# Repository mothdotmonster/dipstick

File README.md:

# WARNING!
when i ordered a batch of these they didn't work and i have no idea why, i think the chips might just have been busted.

do not follow this design as a reference at all. i am only leaving it up for archival purposes.
# dipstick
DIP-sized attinyxx6 breakout board with USB-C

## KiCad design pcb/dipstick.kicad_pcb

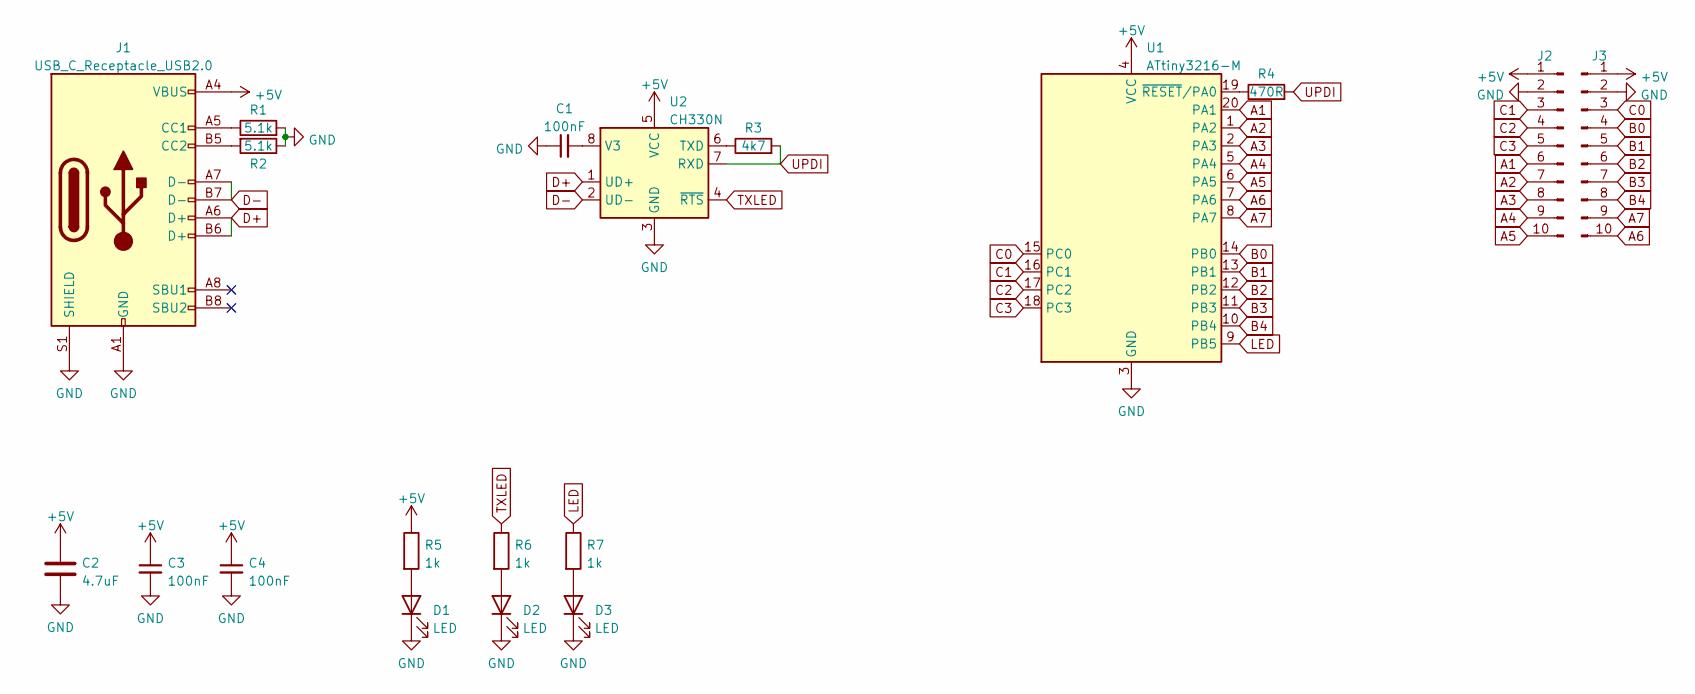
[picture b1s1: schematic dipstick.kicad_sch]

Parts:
C1, C3, C4: 100nF; C_0402_1005Metric; JLC C1525
C2: 4.7uF; C_0402_1005Metric; JLC C23733
D1, D2, D3: LED; LED_0603_1608Metric; JLC C2286
J1: USB_C_Receptacle_USB2.0; USB_C_Receptacle_HRO_TYPE-C-31-M-12; JLC C165948
J2, J3: Conn_01x10_Male; PinHeader_1x10_P2.54mm_Vertical
R1, R2: 5.1k; R_0402_1005Metric; JLC C25905
R3: 4k7; R_0402_1005Metric; JLC C25900
R4: 470R; R_0402_1005Metric; JLC C25117
R5, R6, R7: 1k; R_0402_1005Metric; JLC C11702
U1: ATtiny3216-M; VQFN-20-1EP_3x3mm_P0.4mm_EP1.7x1.7mm; JLC C507118
U2: CH330N; SOIC-8_3.9x4.9mm_P1.27mm; JLC C2977777

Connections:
+5V: C2.1, C3.1, C4.1, J1.A4 (VBUS), J1.A9 (VBUS), J1.B4 (VBUS), J1.B9 (VBUS), J2.1, J3.1, R5.1, U1.4 (VCC), U2.5 (VCC)
A1: J2.6, U1.20 (PA1)
A2: J2.7, U1.1 (PA2)
A3: J2.8, U1.2 (PA3)
A4: J2.9, U1.5 (PA4)
A5: J2.10, U1.6 (PA5)
A6: J3.10, U1.7 (PA6)
A7: J3.9, U1.8 (PA7)
B0: J3.4, U1.14 (PB0)
B1: J3.5, U1.13 (PB1)
B2: J3.6, U1.12 (PB2)
B3: J3.7, U1.11 (PB3)
B4: J3.8, U1.10 (PB4)
C0: J3.3, U1.15 (PC0)
C1: J2.3, U1.16 (PC1)
C2: J2.4, U1.17 (PC2)
C3: J2.5, U1.18 (PC3)
D+: J1.A6 (D+), J1.B6 (D+), U2.1 (UD+)
D-: J1.A7 (D-), J1.B7 (D-), U2.2 (UD-)
GND: C1.1, C2.2, C3.2, C4.2, D1.1 (K), D2.1 (K), D3.1 (K), J1.A1 (GND), J1.A12 (GND), J1.B1 (GND), J1.B12 (GND), J1.S1 (SHIELD), J2.2, J3.2, R1.2, R2.1, U1.3 (GND), U1.21 (GND), U2.3 (GND)
LED: R7.1, U1.9 (PB5)
unnamed: D1.2 (A), R5.2
unnamed: D2.2 (A), R6.2
unnamed: D3.2 (A), R7.2
unnamed: J1.A5 (CC1), R1.1
unnamed: J1.B5 (CC2), R2.2
unnamed: R4.1, U1.19 (~RESET/PA0)
unnamed: R3.1, U2.6 (TXD)
unnamed: C1.2, U2.8 (V3)
TXLED: R6.1, U2.4 (~RTS)
UPDI: R3.2, R4.2, U2.7 (RXD)

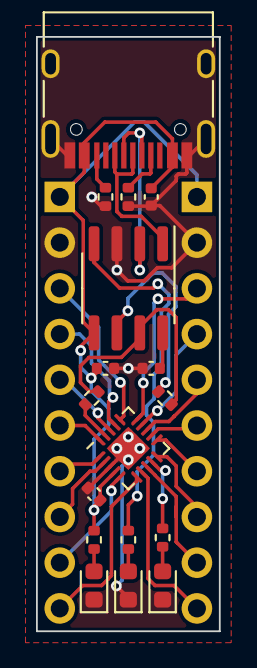
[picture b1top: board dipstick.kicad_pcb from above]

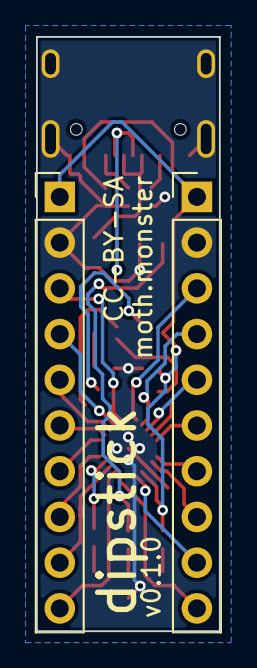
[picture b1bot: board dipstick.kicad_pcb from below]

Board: 2 copper layers, 10.2 x 33.0 mm, 19 parts (2 on the bottom side), 31 nets.

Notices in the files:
pcb/dipstick.kicad_pcb:
CC-BY-SA
